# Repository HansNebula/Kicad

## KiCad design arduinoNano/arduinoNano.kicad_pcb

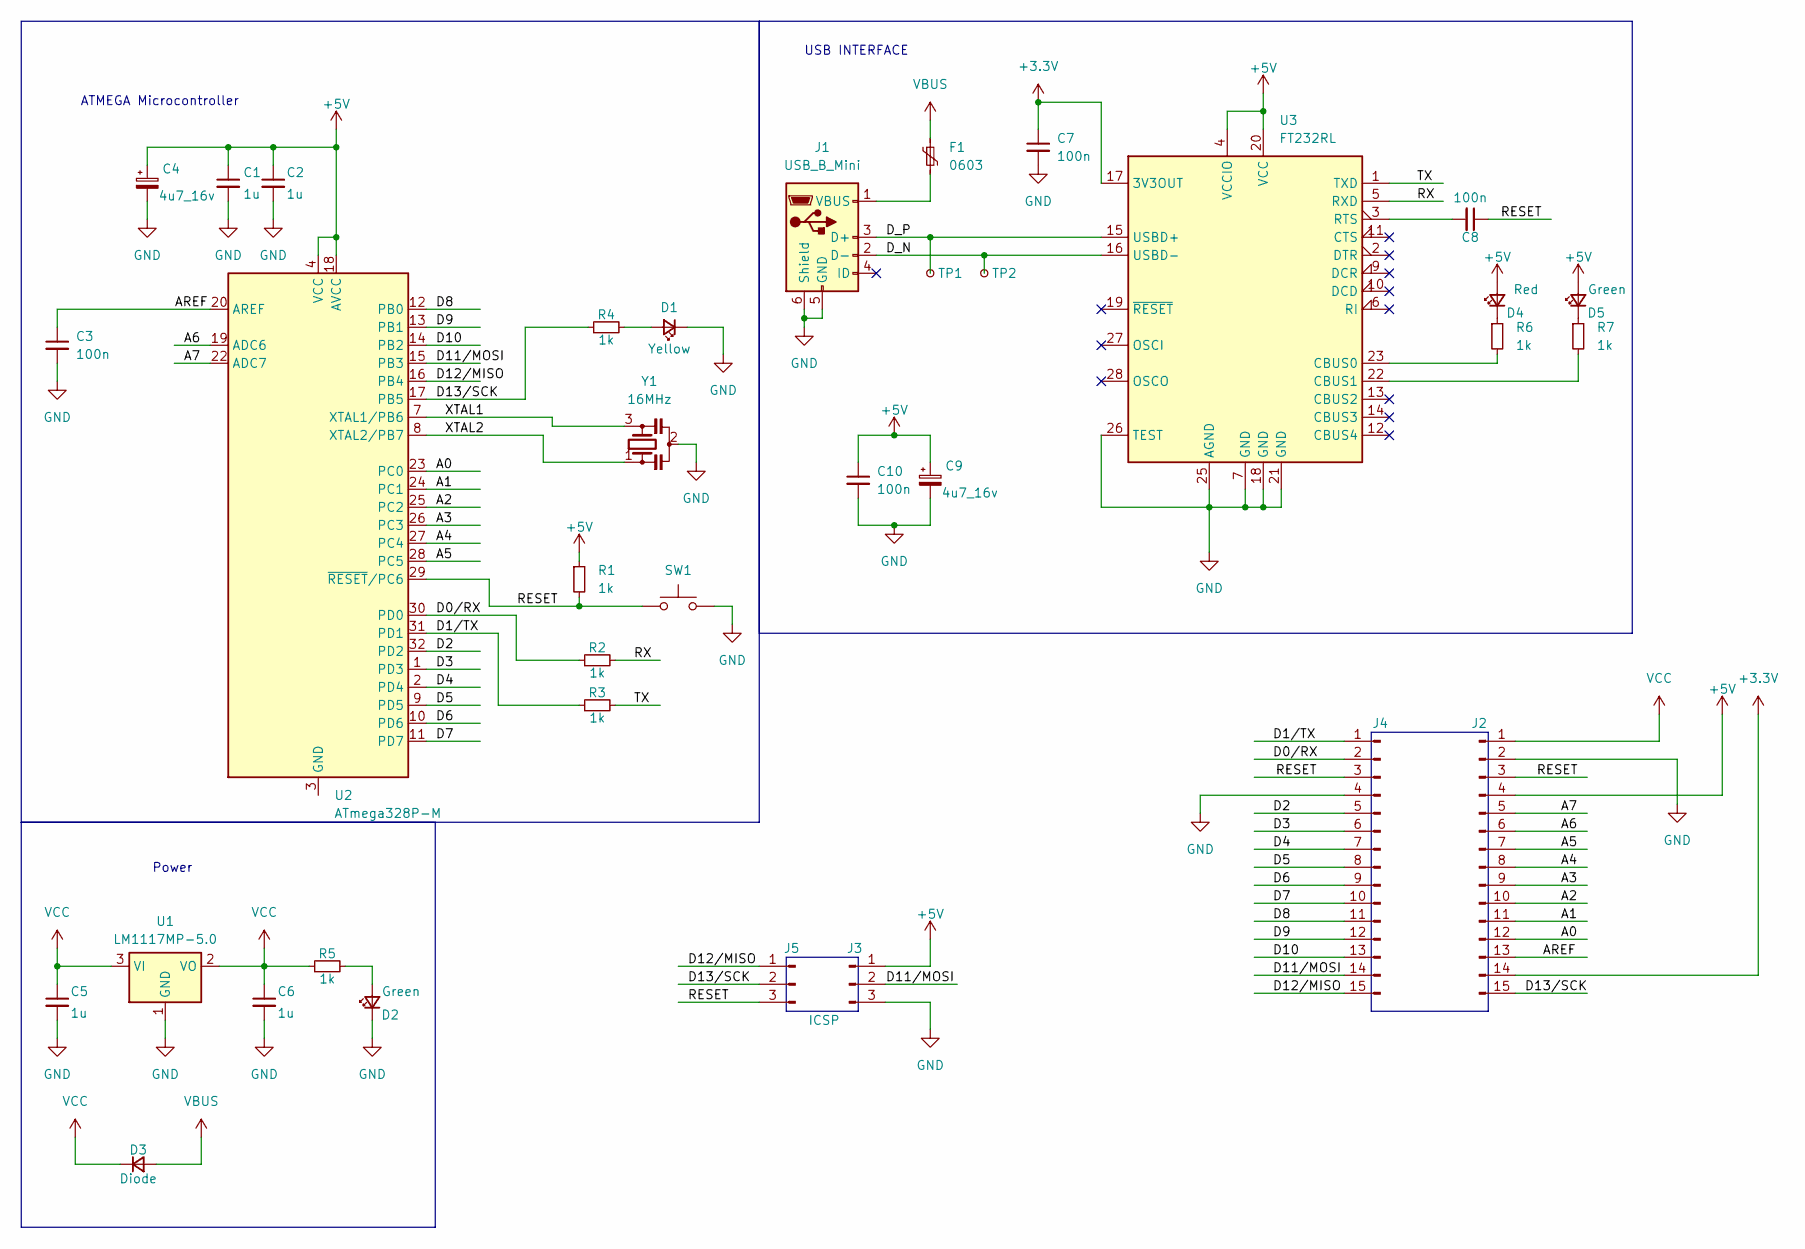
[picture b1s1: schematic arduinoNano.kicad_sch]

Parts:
C1, C2, C5, C6: 1u; C_0603_1608Metric
C3, C7, C8, C10: 100n; C_0603_1608Metric
C4, C9: 4u7_16v; CP_EIA-3216-10_Kemet-I
D1: Yellow; LED_0805_2012Metric
D2, D5: Green; LED_0805_2012Metric
D3: Diode; D_MicroSMP_AK
D4: Red; LED_0805_2012Metric
F1: 0603; D_0603_1608Metric
J1: USB_B_Mini; USB_Mini-B_Lumberg_2486_01_Horizontal
J2, J4: Conn_01x15_Pin; PinHeader_1x15_P2.54mm_Vertical
J3, J5: ICSP; PinHeader_1x03_P2.54mm_Vertical
R1, R2, R3, R4, R5, R6, R7: 1k; D_0603_1608Metric
SW1: SW_Push; Panasonic_EVQPUJ_EVQPUA
TP1, TP2: TestPoint_Small; TestPoint_Pad_D1.0mm
U1: LM1117MP-5.0; SOT-223-3_TabPin2
U2: ATmega328P-M; QFN-32-1EP_5x5mm_P0.5mm_EP3.1x3.1mm
U3: FT232RL; SSOP-28_5.3x10.2mm_P0.65mm
Y1: 16MHz; Resonator_SMD_Murata_CSTxExxV-3Pin_3.0x1.1mm

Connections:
+3.3V: C7.1, J2.14, U3.17 (3V3OUT)
+5V: C1.1, C2.1, C4.1, C9.1, C10.1, D4.2 (A), D5.2 (A), J2.4, J3.1, R1.1, U2.4 (VCC), U2.6 (VCC), U2.18 (AVCC), U3.4 (VCCIO), U3.20 (VCC)
/A0: J2.12, U2.23 (PC0)
/A1: J2.11, U2.24 (PC1)
/A2: J2.10, U2.25 (PC2)
/A3: J2.9, U2.26 (PC3)
/A4: J2.8, U2.27 (PC4)
/A5: J2.7, U2.28 (PC5)
/A6: J2.6, U2.19 (ADC6)
/A7: J2.5, U2.22 (ADC7)
/AREF: C3.1, J2.13, U2.20 (AREF)
/D0/RX: J4.2, R2.1, U2.30 (PD0)
/D1/TX: J4.1, R3.1, U2.31 (PD1)
/D2: J4.5, U2.32 (PD2)
/D3: J4.6, U2.1 (PD3)
/D4: J4.7, U2.2 (PD4)
/D5: J4.8, U2.9 (PD5)
/D6: J4.9, U2.10 (PD6)
/D7: J4.10, U2.11 (PD7)
/D8: J4.11, U2.12 (PB0)
/D9: J4.12, U2.13 (PB1)
/D10: J4.13, U2.14 (PB2)
/D11/MOSI: J3.2, J4.14, U2.15 (PB3)
/D12/MISO: J4.15, J5.1, U2.16 (PB4)
/D13/SCK: J2.15, J5.2, R4.1, U2.17 (PB5)
/D_N: J1.2 (D-), TP2.1, U3.16 (USBD-)
/D_P: J1.3 (D+), TP1.1, U3.15 (USBD+)
/RESET: C8.1, J2.3, J4.3, J5.3, R1.2, SW1.1, U2.29 (~RESET/PC6)
/RX: R2.2, U3.5 (RXD)
/TX: R3.2, U3.1 (TXD)
/XTAL1: U2.7 (XTAL1/PB6), Y1.3
/XTAL2: U2.8 (XTAL2/PB7), Y1.1
GND: C1.2, C2.2, C3.2, C4.2, C5.2, C6.2, C7.2, C9.2, C10.2, D1.1 (K), D2.1 (K), J1.5 (GND), J1.6 (Shield), J2.2, J3.3, J4.4, SW1.2, U1.1 (GND), U3.7 (GND), U3.18 (GND), U3.21 (GND), U3.25 (AGND), U3.26 (TEST), Y1.2
unnamed: D1.2 (A), R4.2
unnamed: D2.2 (A), R5.2
unnamed: D4.1 (K), R6.1
unnamed: D5.1 (K), R7.1
unnamed: F1.2, J1.1 (VBUS)
unnamed: U2.3 (GND), U2.5 (GND), U2.21 (GND), U2.33 (GND)
unnamed: R6.2, U3.23 (CBUS0)
unnamed: R7.2, U3.22 (CBUS1)
unnamed: C8.2, U3.3 (RTS)
VBUS: D3.2 (A), F1.1
VCC: C5.1, C6.1, D3.1 (K), J2.1, R5.1, U1.2 (VO), U1.3 (VI)

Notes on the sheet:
Power
USB INTERFACE
ATMEGA Microcontroller

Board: 4 copper layers, 35 parts (16 on the bottom side), 44 nets, no tracks yet.

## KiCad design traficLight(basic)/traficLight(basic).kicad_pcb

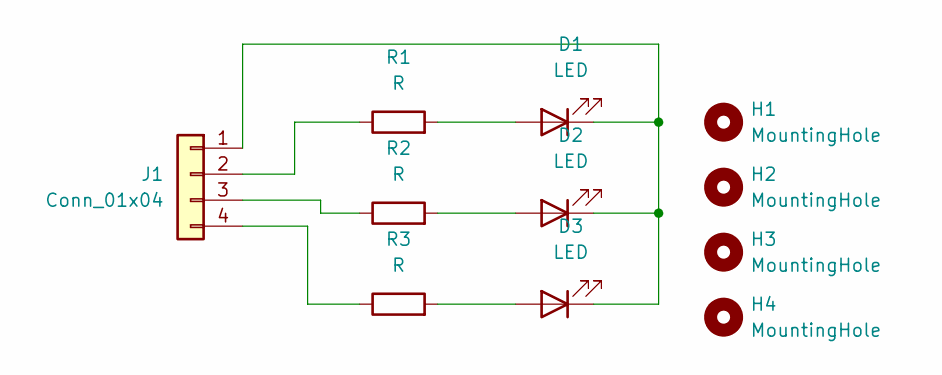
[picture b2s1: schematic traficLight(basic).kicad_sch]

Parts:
D1, D2, D3: LED; LED_D3.0mm
H1, H2, H3, H4: MountingHole; MountingHole_2.5mm_Pad
J1: Conn_01x04; PinHeader_1x04_P2.54mm_Horizontal
R1, R2, R3: R; R_Axial_DIN0204_L3.6mm_D1.6mm_P5.08mm_Horizontal

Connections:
unnamed: D1.2 (A), R1.2
unnamed: D1.1 (K), D2.1 (K), D3.1 (K), J1.1
unnamed: D2.2 (A), R2.2
unnamed: D3.2 (A), R3.2
unnamed: J1.2, R1.1
unnamed: J1.3, R2.1
unnamed: J1.4, R3.1

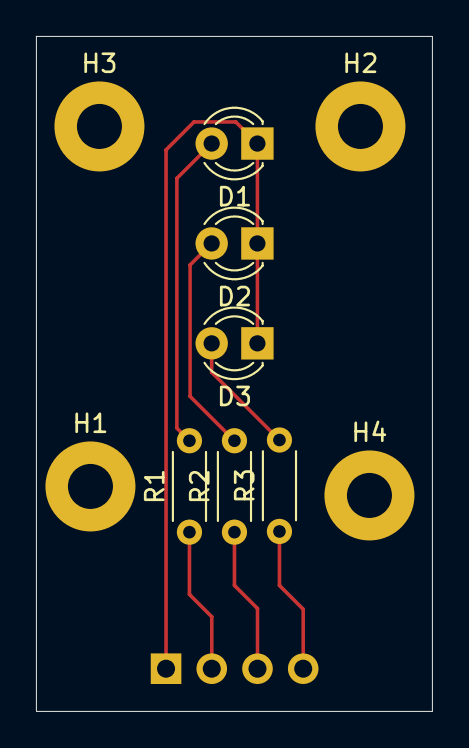
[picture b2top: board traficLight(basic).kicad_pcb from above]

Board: 2 copper layers, 22.0 x 37.5 mm, 11 parts (1 on the bottom side), 7 nets.

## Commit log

2024-05-30 initial
2024-06-02 done schematic. still in pcb designing not done yet
2024-06-02 pcb design in process
2024-06-03 Done designing, next will be wiring
